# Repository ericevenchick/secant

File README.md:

# seCANt

A two bus CAN tool based on the TI Tiva C microcontroller.

## Files
- hw/ - hardware design files (KiCad)
- fw/ - firmware source

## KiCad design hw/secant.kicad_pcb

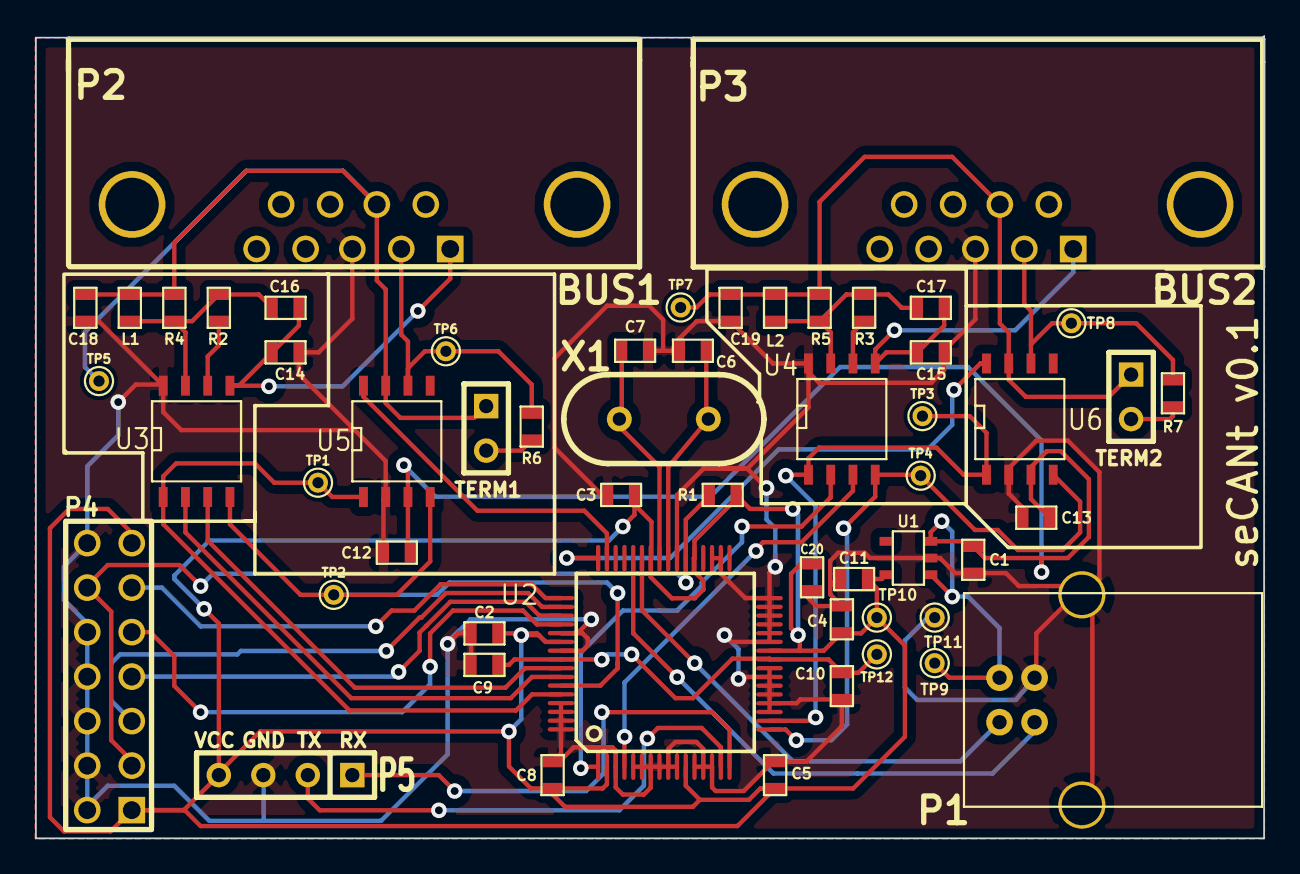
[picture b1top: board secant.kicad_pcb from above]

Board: 2 copper layers, 70.1 x 45.8 mm, 55 parts (0 on the bottom side), 37 nets.

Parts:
C1: C; SM0603
C2, C3, C4, C5, C10, C12, C13, C14, C15, C20: 0.1uF; SM0603
C6, C7: ?pF; SM0603
C8, C11: 1uF; SM0603
C9: 2.2uF; SM0603
C16, C17, C18, C19: 100pF; SM0603
L1, L2: 47 uH; SM0603
P1: USB; USB_B
P2: BUS1; DB9MC
P3: BUS2; DB9MC
P4: JTAG; pin_array_7x2
P5: UART; SIL-4
R1: 10k; SM0603
R2, R3: 6.49k; SM0603
R4, R5: 1k; SM0603
R6, R7: 120; SM0603
TERM1: BUS1 TERM; SIL-2
TERM2: BUS2 TERM; SIL-2
TP1, TP2, TP3, TP4, TP5, TP6, TP7, TP8, TP9, TP10, TP11, TP12: TST; PINTST
U1: TLV70033QDDCRQ1; SOT23-5
U2: TM4C123GE6PMI; TQFP_64
U3, U4: NCV7356; SO8N
U5, U6: TJA1051T; SO8N
X1: 16 MHz; HC-49V

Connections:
+1.2V: C9.1, C10.1, TP12.1, U2.25, U2.56
+3.3V: C2.1, C3.1, C4.1, C5.1, C8.1, C11.1, C20.1, P4.1, P4.13, P5.4, R1.1, TP10.1, U1.5, U2.2, U2.11, U2.26, U2.37, U2.42, U2.54
+5V: C1.1, C12.1, C13.1, P1.1, TP9.1, U1.1, U1.3, U5.3, U6.3
/BUS1H: C18.2, L1.2, P2.7, R4.2, TERM1.1, TP5.1, U5.7
/BUS1L: P2.2, R6.1, TP6.1, U5.6
/BUS1V+: C14.1, C16.2, P2.1, U3.5
/BUS2H: C19.2, L2.2, P3.7, R5.2, TERM2.1, TP7.1, U6.7
/BUS2L: P3.2, R7.1, TP8.1, U6.6
/BUS2V+: C15.1, C17.2, P3.1, U4.5
/CAN0MODE0: U2.58, U3.2
/CAN0MODE1: U2.57, U3.3
/CAN0Rx: TP2.1, U2.59, U3.4, U5.4
/CAN0S: U2.47, U5.8
/CAN0Tx: TP1.1, U2.60, U3.1, U5.1
/CAN1MODE0: U2.1, U4.2
/CAN1MODE1: U2.4, U4.3
/CAN1Rx: TP4.1, U2.17, U4.4, U6.4
/CAN1S: U2.48, U6.8
/CAN1Tx: TP3.1, U2.18, U4.1, U6.1
/JTAG_TCK: P4.9, U2.52
/JTAG_TDI: P4.5, U2.50
/JTAG_TDO: P4.11, U2.49
/JTAG_TMS: P4.7, U2.51
/RESET: P4.3, P4.12, R1.2, U2.38
/U1Rx: P5.1, U2.16
/U1Tx: P5.2, U2.15
/USB0DM: P1.2, U2.43
/USB0DP: P1.3, U2.44
GND: C1.2, C2.2, C3.2, C4.2, C5.2, C6.1, C7.2, C8.2, C9.2, C10.2, C11.2, C12.2, C13.2, C14.2, C15.2, C18.1, C19.1, C20.2, P1.4, P1.5, P1.6, P2.3, P3.3, P4.2, P4.4, P4.6, P4.8, P4.10, P4.14, P5.3, TP11.1, U1.2, U2.3, U2.5, U2.6, U2.7, U2.8, U2.9, U2.10, U2.12, U2.13, U2.14, U2.19, U2.20, U2.21, U2.22, U2.23, U2.24, U2.27, U2.28, U2.29, U2.30, U2.31, U2.32, U2.34, U2.35, U2.39, U2.53, U2.55, U2.61, U2.62, U2.63, U2.64, U3.8, U4.8, U5.2, U6.2
unnamed: R3.1, U4.6
unnamed: C17.1, L2.1, R3.2, R5.1, U4.7
unnamed: R7.2, TERM2.2
unnamed: R6.2, TERM1.2
unnamed: R2.1, U3.6
unnamed: C16.1, L1.1, R2.2, R4.1, U3.7
unnamed: C7.1, U2.41, X1.1
unnamed: C6.2, U2.40, X1.2

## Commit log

2014-03-25 added basic can functionality
2014-03-25 added ignore for vim .swp files
2014-03-25 can bus setting and tx working
2014-03-28 added receiving for CAN0
2014-03-28 changed from DOS to UNIX line endings
2014-04-05 moved buffer size to usb.h
2014-04-05 added support for filters
2014-04-05 receive buffers instead of single characters
2014-04-07 moved firmware to own directory
2014-04-07 added draft schematic
2014-04-07 added readme
2014-04-09 seperated .gitignores
2014-04-09 added first PCB layout
2014-04-09 deleted unused mod file
2014-04-10 fixed U2 LDO pins
2014-04-10 updated part numbers for BOM
2014-04-10 updated mfg part numbers
